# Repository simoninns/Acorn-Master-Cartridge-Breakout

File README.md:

# Acorn-Master-Cartridge-Breakout
A breakout adapter for the Acorn Master 128 cartridge interface for connection to a breadboard

## Synopsis

This card is designed to allow connection between an Acorn BBC Master's cartridge interface and an electronics breadboard.  To save production cost the board is designed as two PCBs.  The cartridge header should be produced with a gold finish due to the edge connector (this is not required for the breadboard header).

## Motivation

Prototyping new Acorn BBC Master hardware.

## Author

The Acorn Master Cartridge Breakout board was designed by Simon Inns.

## License

This project is released under a Creative Commons Attribution-ShareAlike 4.0 International (CC BY-SA 4.0) licence.

You are free to:

Share — copy and redistribute the material in any medium or format
Adapt — remix, transform, and build upon the material
for any purpose, even commercially.

This license is acceptable for Free Cultural Works.

The licensor cannot revoke these freedoms as long as you follow the license terms.

Under the following terms:

Attribution — You must give appropriate credit, provide a link to the license,
and indicate if changes were made. You may do so in any reasonable manner, but
not in any way that suggests the licensor endorses you or your use.

ShareAlike — If you remix, transform, or build upon the material, you must
distribute your contributions under the same license as the original.

No additional restrictions — You may not apply legal terms or technological
measures that legally restrict others from doing anything the license permits.

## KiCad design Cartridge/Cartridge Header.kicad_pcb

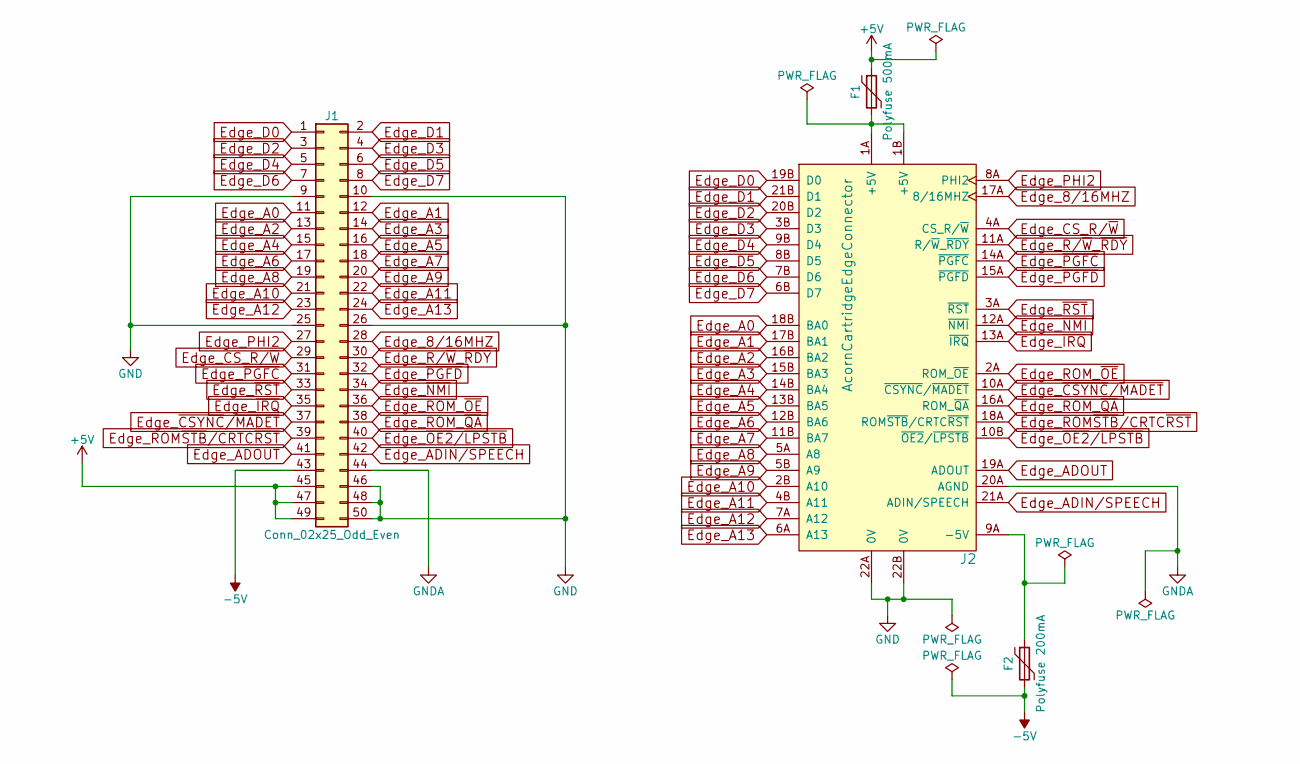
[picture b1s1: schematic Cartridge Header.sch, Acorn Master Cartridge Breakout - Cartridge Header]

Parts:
F1: Polyfuse 500mA; Fuse_SMD1206_HandSoldering
F2: Polyfuse 200mA; Fuse_SMD1206_HandSoldering
J1: Conn_02x25_Odd_Even; IDC-Header_2x25_Pitch2.54mm_Straight
J2: AcornCartridgeEdgeConnector; Acorn_Cartridge

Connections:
+5V: F1.1, J1.45, J1.47, J1.49
-5V: F2.2, J1.43
Edge_8/16MHZ: J1.28, J2.17A (8/16MHZ)
Edge_A0: J1.11, J2.18B (BA0)
Edge_A1: J1.12, J2.17B (BA1)
Edge_A2: J1.13, J2.16B (BA2)
Edge_A3: J1.14, J2.15B (BA3)
Edge_A4: J1.15, J2.14B (BA4)
Edge_A5: J1.16, J2.13B (BA5)
Edge_A6: J1.17, J2.12B (BA6)
Edge_A7: J1.18, J2.11B (BA7)
Edge_A8: J1.19, J2.5A (A8)
Edge_A9: J1.20, J2.5B (A9)
Edge_A10: J1.21, J2.2B (A10)
Edge_A11: J1.22, J2.4B (A11)
Edge_A12: J1.23, J2.7A (A12)
Edge_A13: J1.24, J2.6A (A13)
Edge_ADIN/SPEECH: J1.42, J2.21A (ADIN/SPEECH)
Edge_ADOUT: J1.41, J2.19A (ADOUT)
Edge_CS_R/~W: J1.29, J2.4A (CS_R/~W)
Edge_D0: J1.1, J2.19B (D0)
Edge_D1: J1.2, J2.21B (D1)
Edge_D2: J1.3, J2.20B (D2)
Edge_D3: J1.4, J2.3B (D3)
Edge_D4: J1.5, J2.9B (D4)
Edge_D5: J1.6, J2.8B (D5)
Edge_D6: J1.7, J2.7B (D6)
Edge_D7: J1.8, J2.6B (D7)
Edge_PHI2: J1.27, J2.8A (PHI2)
Edge_R/~W~_~RDY: J1.30, J2.11A (R/~W~_~RDY)
Edge_ROM_~OE: J1.36, J2.2A (ROM_~OE)
Edge_ROM_~QA: J1.38, J2.16A (ROM_~QA)
Edge_ROM~STB~/CRTC~RST: J1.39, J2.18A (ROM~STB~/CRTC~RST)
Edge_~CSYNC~/~MADET: J1.37, J2.10A (~CSYNC~/~MADET)
Edge_~IRQ: J1.35, J2.13A (~IRQ)
Edge_~NMI: J1.34, J2.12A (~NMI)
Edge_~OE2~/~LPSTB: J1.40, J2.10B (~OE2~/~LPSTB)
Edge_~PGFC: J1.31, J2.14A (~PGFC)
Edge_~PGFD: J1.32, J2.15A (~PGFD)
Edge_~RST: J1.33, J2.3A (~RST)
GND: J1.9, J1.10, J1.25, J1.26, J1.46, J1.48, J1.50, J2.22A (0V), J2.22B (0V)
GNDA: J1.44, J2.20A (AGND)
unnamed: F1.2, J2.1A (+5V), J2.1B (+5V)
unnamed: F2.1, J2.9A (-5V)

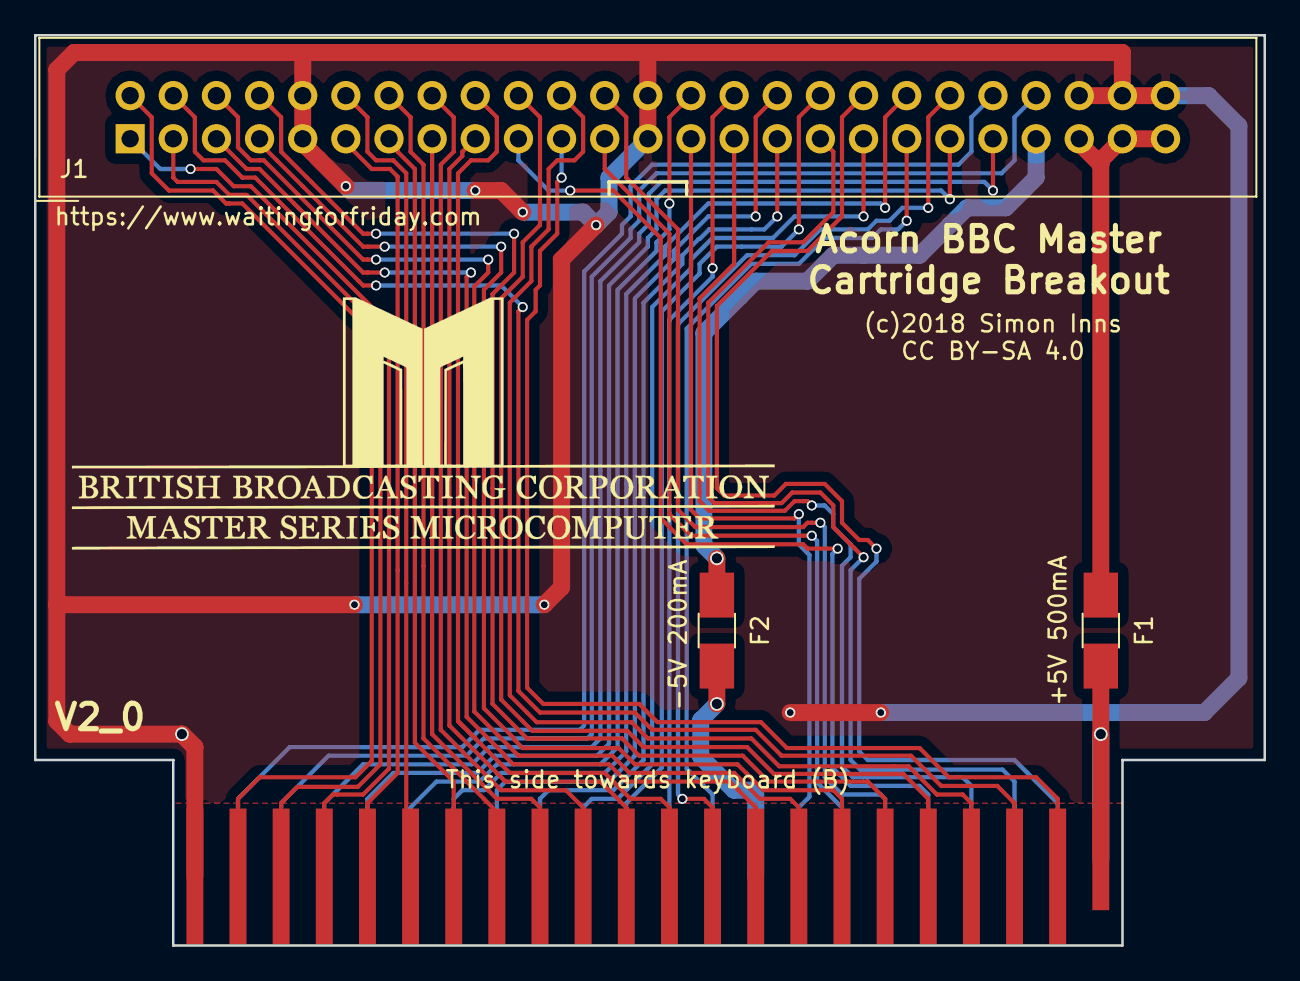
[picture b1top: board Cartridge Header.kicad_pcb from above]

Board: 2 copper layers, 72.4 x 53.6 mm, 4 parts (0 on the bottom side), 44 nets.

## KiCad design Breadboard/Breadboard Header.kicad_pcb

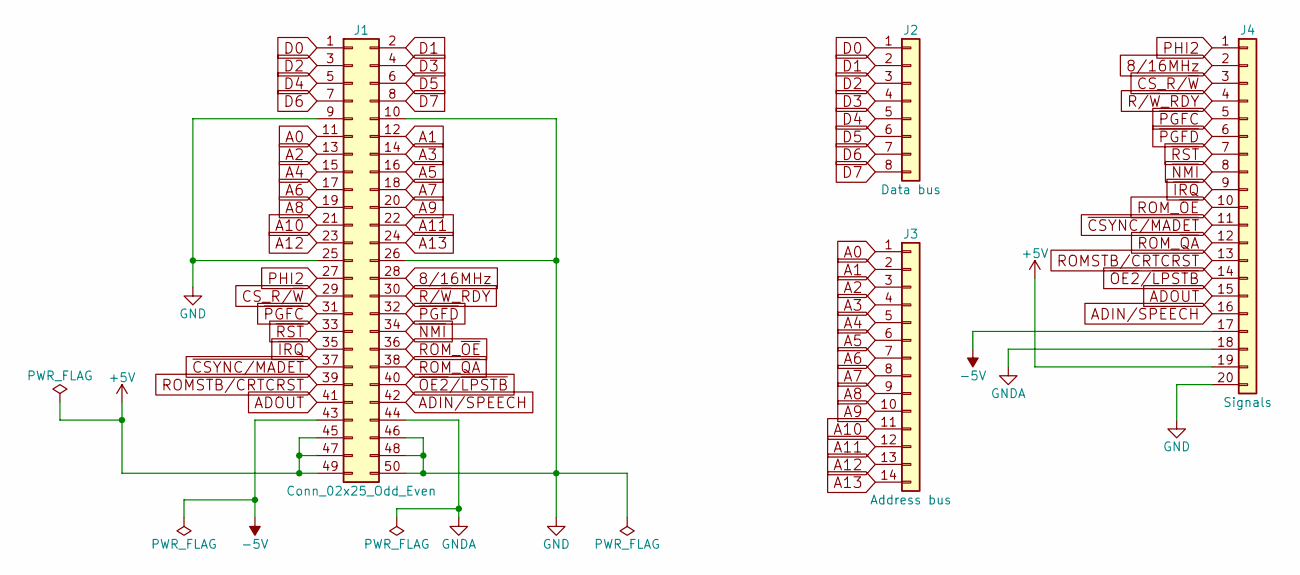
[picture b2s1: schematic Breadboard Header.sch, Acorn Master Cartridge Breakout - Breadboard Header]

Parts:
J1: Conn_02x25_Odd_Even; IDC-Header_2x25_Pitch2.54mm_Straight
J2: Data bus; Pin_Header_Straight_1x08_Pitch2.54mm
J3: Address bus; Pin_Header_Straight_1x14_Pitch2.54mm
J4: Signals; Pin_Header_Straight_1x20_Pitch2.54mm

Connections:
8/16MHz: J1.28, J4.2
+5V: J1.45, J1.47, J1.49, J4.19
-5V: J1.43, J4.17
A0: J1.11, J3.1
A1: J1.12, J3.2
A2: J1.13, J3.3
A3: J1.14, J3.4
A4: J1.15, J3.5
A5: J1.16, J3.6
A6: J1.17, J3.7
A7: J1.18, J3.8
A8: J1.19, J3.9
A9: J1.20, J3.10
A10: J1.21, J3.11
A11: J1.22, J3.12
A12: J1.23, J3.13
A13: J1.24, J3.14
ADIN/SPEECH: J1.42, J4.16
ADOUT: J1.41, J4.15
CS_R/~W: J1.29, J4.3
D0: J1.1, J2.1
D1: J1.2, J2.2
D2: J1.3, J2.3
D3: J1.4, J2.4
D4: J1.5, J2.5
D5: J1.6, J2.6
D6: J1.7, J2.7
D7: J1.8, J2.8
GND: J1.9, J1.10, J1.25, J1.26, J1.46, J1.48, J1.50, J4.20
GNDA: J1.44, J4.18
PHI2: J1.27, J4.1
R/~W~_RDY: J1.30, J4.4
ROMSTB/CRTCRST: J1.39, J4.13
ROM_~OE: J1.36, J4.10
ROM_~QA: J1.38, J4.12
~CSYNC/MADET: J1.37, J4.11
~IRQ: J1.35, J4.9
~NMI: J1.34, J4.8
~OE2~/~LPSTB: J1.40, J4.14
~PGFC: J1.31, J4.5
~PGFD: J1.32, J4.6
~RST: J1.33, J4.7

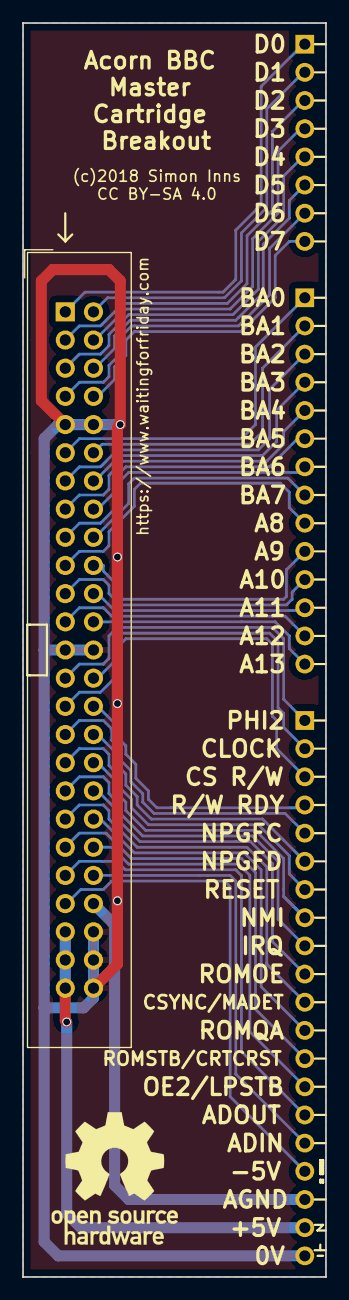
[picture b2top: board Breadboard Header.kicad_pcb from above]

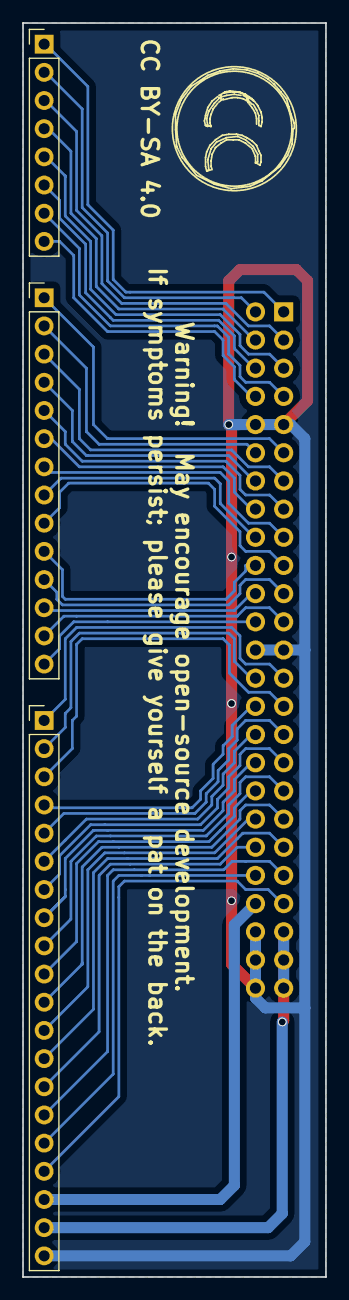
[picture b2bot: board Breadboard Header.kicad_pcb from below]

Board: 2 copper layers, 27.3 x 113.0 mm, 5 parts (4 on the bottom side), 42 nets.

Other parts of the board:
CC BY-SA 4.0: Symbol_CreativeCommons_SilkScreenTop_Type2_Big

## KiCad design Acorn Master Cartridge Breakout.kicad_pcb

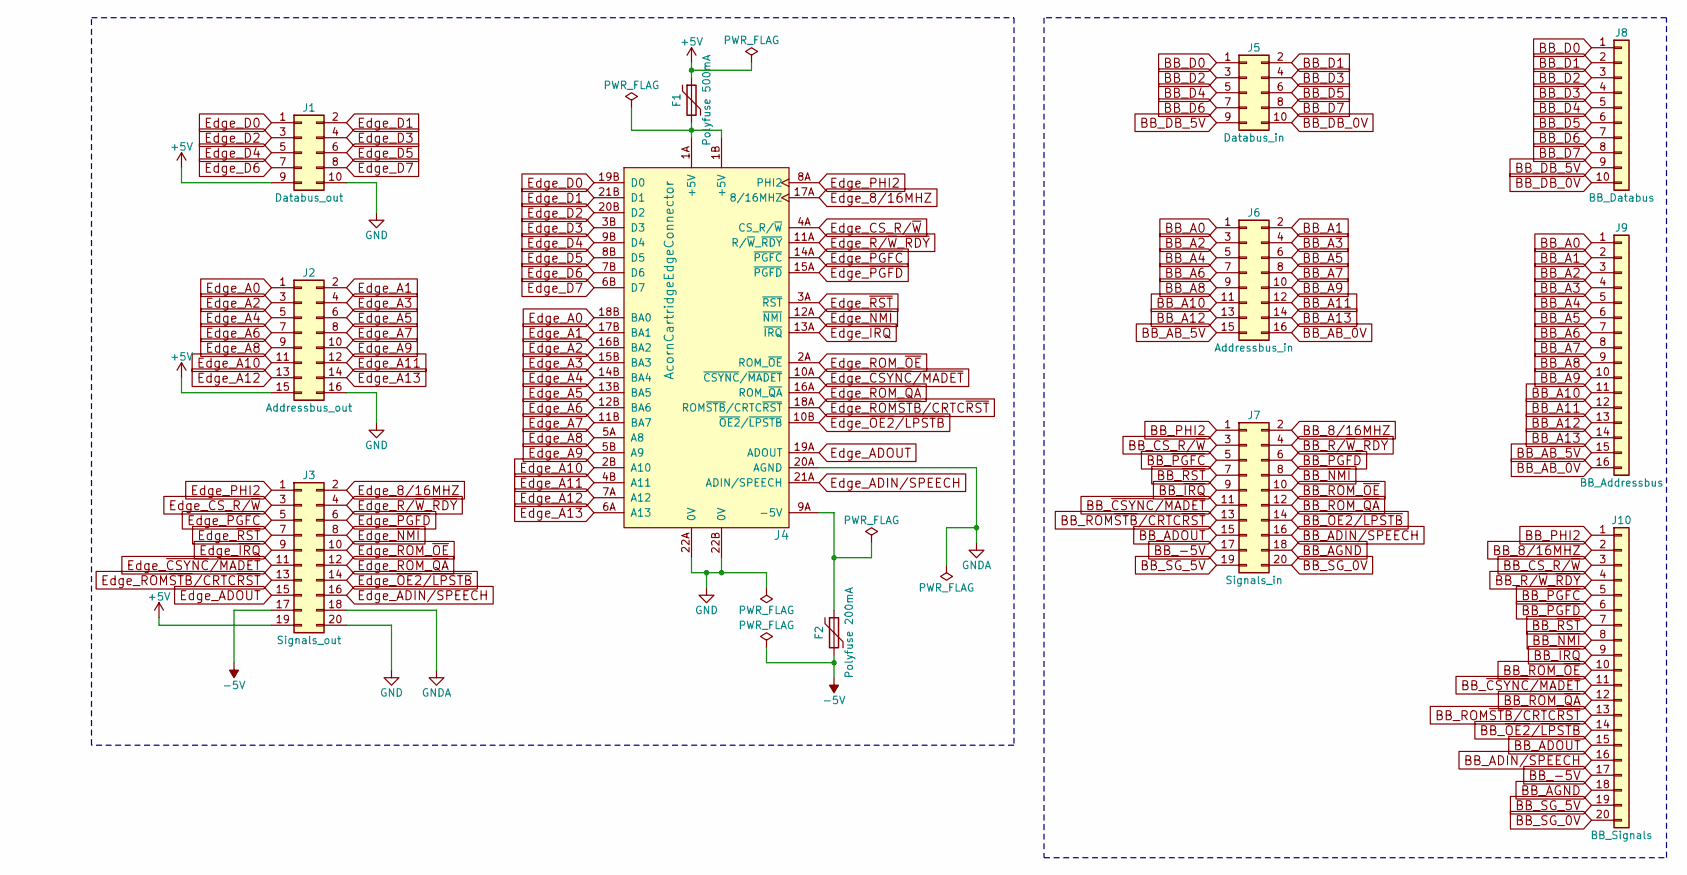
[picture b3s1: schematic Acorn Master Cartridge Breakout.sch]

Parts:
F1: Polyfuse 500mA; Fuse_SMD1206_HandSoldering
F2: Polyfuse 200mA; Fuse_SMD1206_HandSoldering
J1: Databus_out; Multicomp_MC9A22-1034_2x05x2.54mm_Angled
J2: Addressbus_out; Multicomp_MC9A22-1634_2x08x2.54mm_Angled
J3: Signals_out; Multicomp_MC9A22-2034_2x10x2.54mm_Angled
J4: AcornCartridgeEdgeConnector; Acorn_Cartridge
J5: Databus_in; Multicomp_MC9A12-1034_2x05x2.54mm_Straight
J6: Addressbus_in; Multicomp_MC9A12-1634_2x08x2.54mm_Straight
J7: Signals_in; Multicomp_MC9A12-2034_2x10x2.54mm_Straight
J8: BB_Databus; Pin_Header_Straight_1x10_Pitch2.54mm
J9: BB_Addressbus; Pin_Header_Straight_1x16_Pitch2.54mm
J10: BB_Signals; Pin_Header_Straight_1x20_Pitch2.54mm

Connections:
+5V: F1.1, J1.9, J2.15, J3.19
-5V: F2.2, J3.17
BB_8/16MHZ: J7.2, J10.2
BB_-5V: J7.17, J10.17
BB_A0: J6.1, J9.1
BB_A1: J6.2, J9.2
BB_A2: J6.3, J9.3
BB_A3: J6.4, J9.4
BB_A4: J6.5, J9.5
BB_A5: J6.6, J9.6
BB_A6: J6.7, J9.7
BB_A7: J6.8, J9.8
BB_A8: J6.9, J9.9
BB_A9: J6.10, J9.10
BB_A10: J6.11, J9.11
BB_A11: J6.12, J9.12
BB_A12: J6.13, J9.13
BB_A13: J6.14, J9.14
BB_AB_0V: J6.16, J9.16
BB_AB_5V: J6.15, J9.15
BB_ADIN/SPEECH: J7.16, J10.16
BB_ADOUT: J7.15, J10.15
BB_AGND: J7.18, J10.18
BB_CS_R/~W: J7.3, J10.3
BB_D0: J5.1, J8.1
BB_D1: J5.2, J8.2
BB_D2: J5.3, J8.3
BB_D3: J5.4, J8.4
BB_D4: J5.5, J8.5
BB_D5: J5.6, J8.6
BB_D6: J5.7, J8.7
BB_D7: J5.8, J8.8
BB_DB_0V: J5.10, J8.10
BB_DB_5V: J5.9, J8.9
BB_PHI2: J7.1, J10.1
BB_R/~W~_~RDY: J7.4, J10.4
BB_ROM_~OE: J7.10, J10.10
BB_ROM_~QA: J7.12, J10.12
BB_ROM~STB~/CRTC~RST: J7.13, J10.13
BB_SG_0V: J7.20, J10.20
BB_SG_5V: J7.19, J10.19
BB_~CSYNC~/~MADET: J7.11, J10.11
BB_~IRQ: J7.9, J10.9
BB_~NMI: J7.8, J10.8
BB_~OE2~/~LPSTB: J7.14, J10.14
BB_~PGFC: J7.5, J10.5
BB_~PGFD: J7.6, J10.6
BB_~RST: J7.7, J10.7
Edge_8/16MHZ: J3.2, J4.17A (8/16MHZ)
Edge_A0: J2.1, J4.18B (BA0)
Edge_A1: J2.2, J4.17B (BA1)
Edge_A2: J2.3, J4.16B (BA2)
Edge_A3: J2.4, J4.15B (BA3)
Edge_A4: J2.5, J4.14B (BA4)
Edge_A5: J2.6, J4.13B (BA5)
Edge_A6: J2.7, J4.12B (BA6)
Edge_A7: J2.8, J4.11B (BA7)
Edge_A8: J2.9, J4.5A (A8)
Edge_A9: J2.10, J4.5B (A9)
Edge_A10: J2.11, J4.2B (A10)
Edge_A11: J2.12, J4.4B (A11)
Edge_A12: J2.13, J4.7A (A12)
Edge_A13: J2.14, J4.6A (A13)
Edge_ADIN/SPEECH: J3.16, J4.21A (ADIN/SPEECH)
Edge_ADOUT: J3.15, J4.19A (ADOUT)
Edge_CS_R/~W: J3.3, J4.4A (CS_R/~W)
Edge_D0: J1.1, J4.19B (D0)
Edge_D1: J1.2, J4.21B (D1)
Edge_D2: J1.3, J4.20B (D2)
Edge_D3: J1.4, J4.3B (D3)
Edge_D4: J1.5, J4.9B (D4)
Edge_D5: J1.6, J4.8B (D5)
Edge_D6: J1.7, J4.7B (D6)
Edge_D7: J1.8, J4.6B (D7)
Edge_PHI2: J3.1, J4.8A (PHI2)
Edge_R/~W~_~RDY: J3.4, J4.11A (R/~W~_~RDY)
Edge_ROM_~OE: J3.10, J4.2A (ROM_~OE)
Edge_ROM_~QA: J3.12, J4.16A (ROM_~QA)
Edge_ROM~STB~/CRTC~RST: J3.13, J4.18A (ROM~STB~/CRTC~RST)
Edge_~CSYNC~/~MADET: J3.11, J4.10A (~CSYNC~/~MADET)
Edge_~IRQ: J3.9, J4.13A (~IRQ)
Edge_~NMI: J3.8, J4.12A (~NMI)
Edge_~OE2~/~LPSTB: J3.14, J4.10B (~OE2~/~LPSTB)
Edge_~PGFC: J3.5, J4.14A (~PGFC)
Edge_~PGFD: J3.6, J4.15A (~PGFD)
Edge_~RST: J3.7, J4.3A (~RST)
GND: J1.10, J2.16, J3.20, J4.22A (0V), J4.22B (0V)
GNDA: J3.18, J4.20A (AGND)
unnamed: F1.2, J4.1A (+5V), J4.1B (+5V)
unnamed: F2.1, J4.9A (-5V)

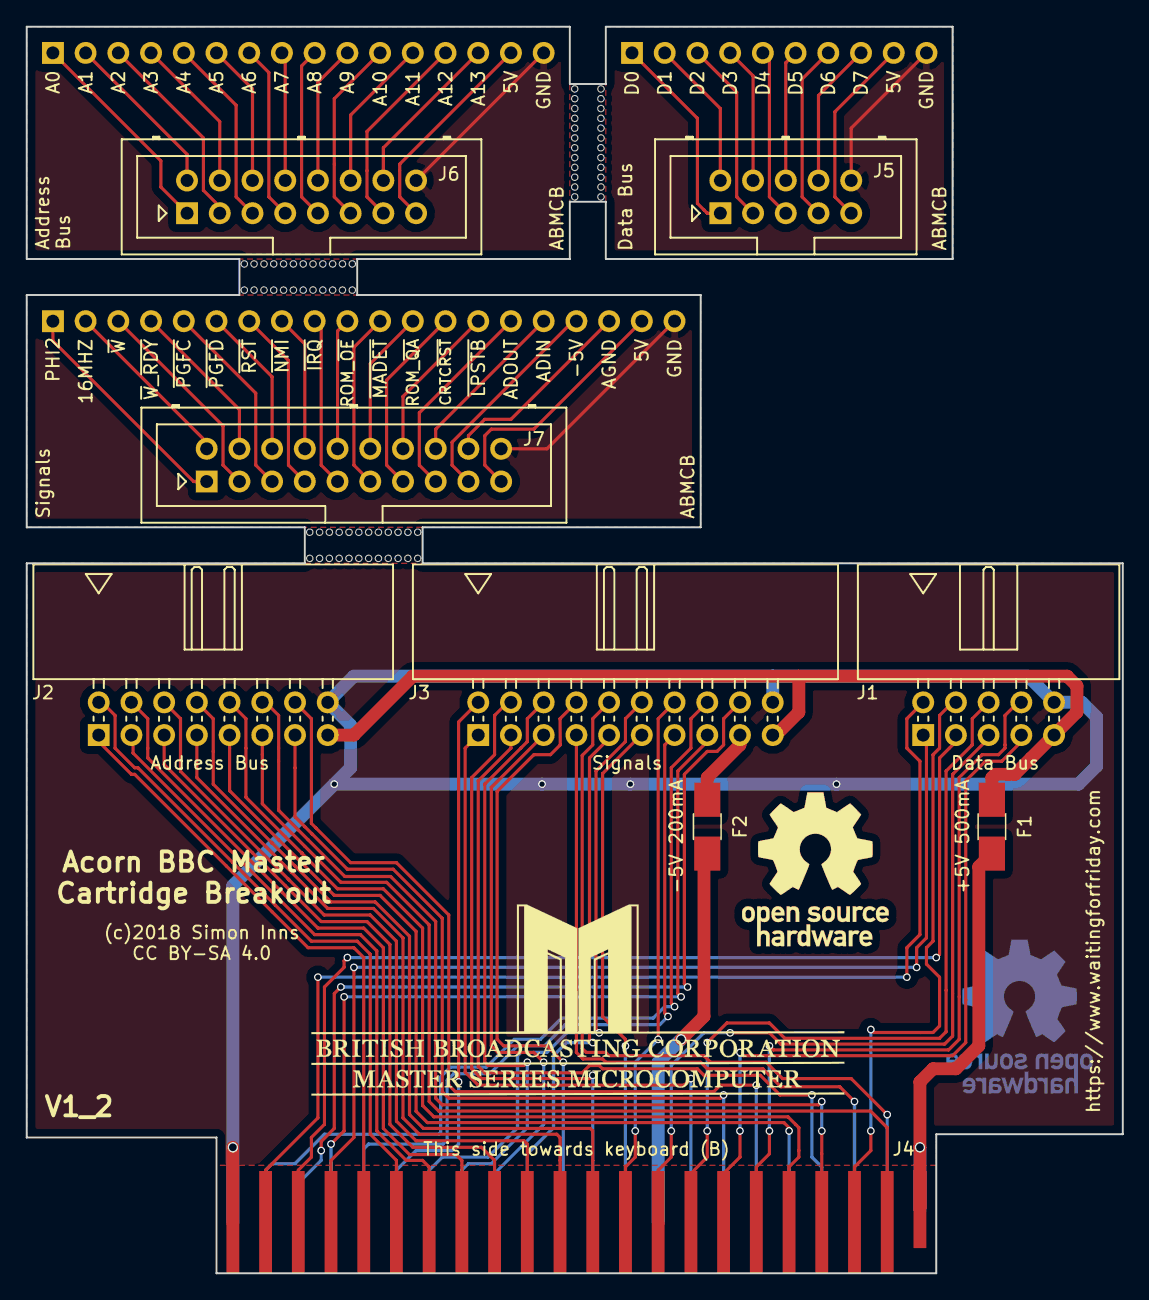
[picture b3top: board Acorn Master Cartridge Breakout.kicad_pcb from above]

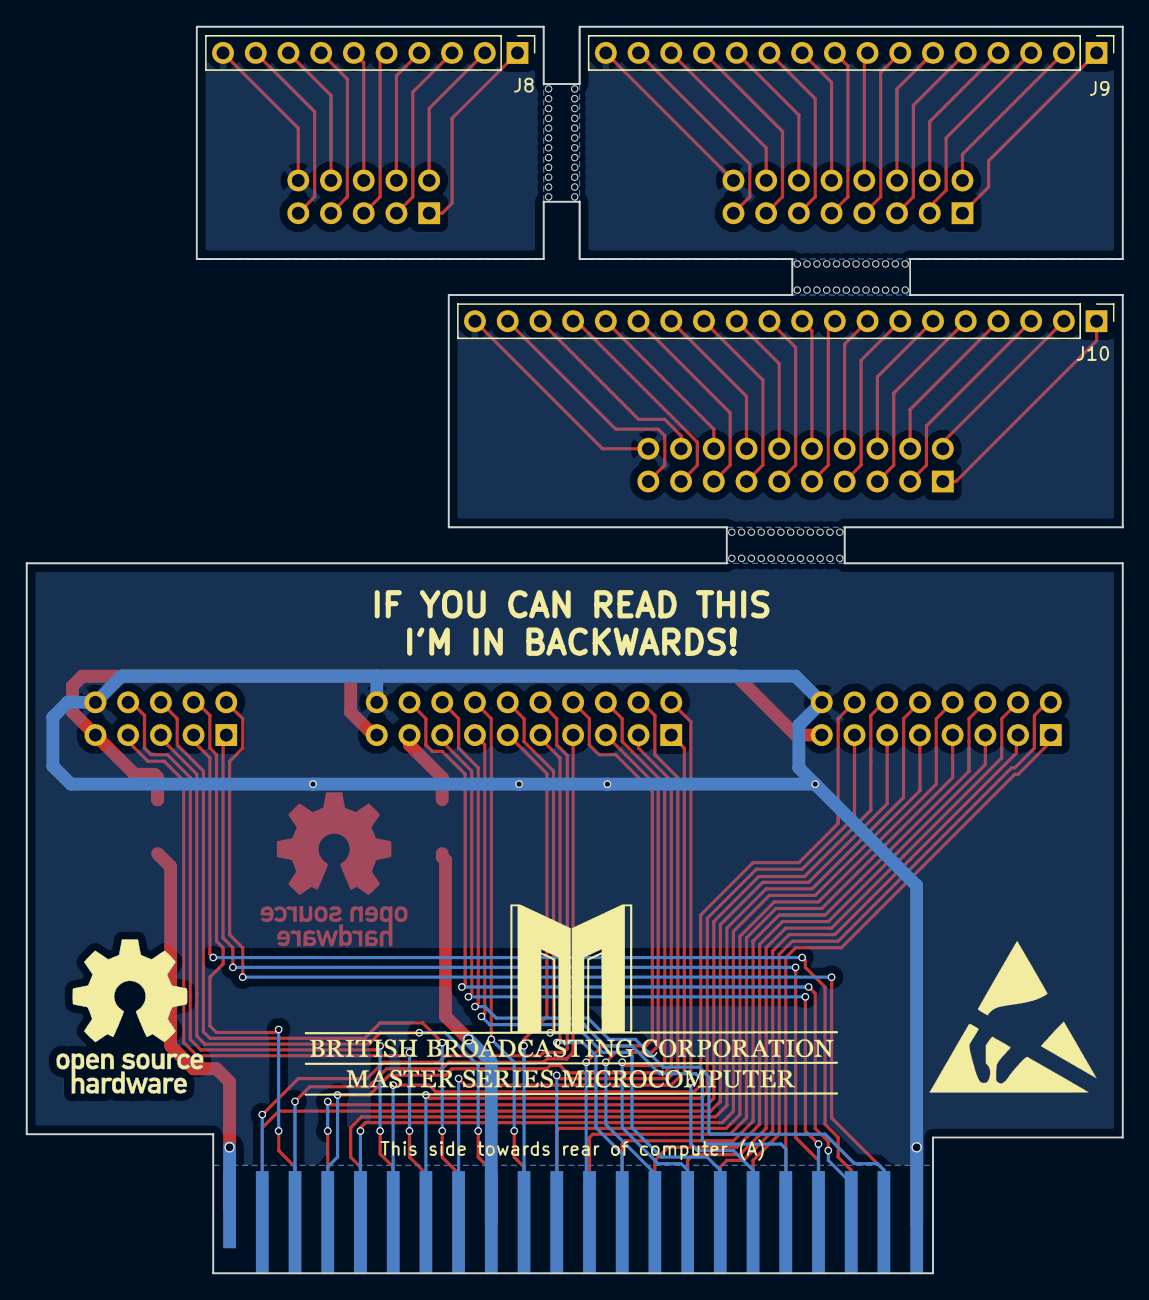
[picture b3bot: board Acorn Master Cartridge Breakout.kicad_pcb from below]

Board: 2 copper layers, 85.1 x 96.8 mm, 12 parts (3 on the bottom side), 90 nets.

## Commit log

2018-05-06 Initial commit of design
2018-05-06 Corrected back PCB image
2018-05-06 Updated with addition edge-cuts to allow the panel to be scored
2018-05-06 Remade as a single panel with silkscreen cut marks
2018-05-06 Updated board image jpegs
2018-05-06 Moved outline and added V-scores for multiple boards
    Note: KiCAD's 3D renderer does not correctly trace the edge-cuts
2018-05-07 New design using mouse-bites and including poly-fuses
2018-05-07 Added missing solder mask Gerbers
2018-05-19 New PCB design to fix #1
2018-05-21 Modified design to provide a continuous external edge cut profile
2018-05-21 Updated PCB images
2018-05-21 Split into two redesigned PCBs
    Seems impossible to get a PCB house to understand that a 10x10 PCB is a single PCB; due to this the breakout adapter has been redesigned as two PCBs interconnected by a 50 way ribbon cable (so you ca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
2018-05-21 Removed unnecessary files

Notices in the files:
Acorn Master Cartridge Breakout.kicad_pcb:
(c)2018 Simon Inns
License: Attribution-ShareAlike (CC BY-SA 4.0)
CC BY-SA 4.0
Acorn Master Cartridge Breakout.sch:
License: Attribution-ShareAlike 4.0 (CC BY-SA 4.0)
